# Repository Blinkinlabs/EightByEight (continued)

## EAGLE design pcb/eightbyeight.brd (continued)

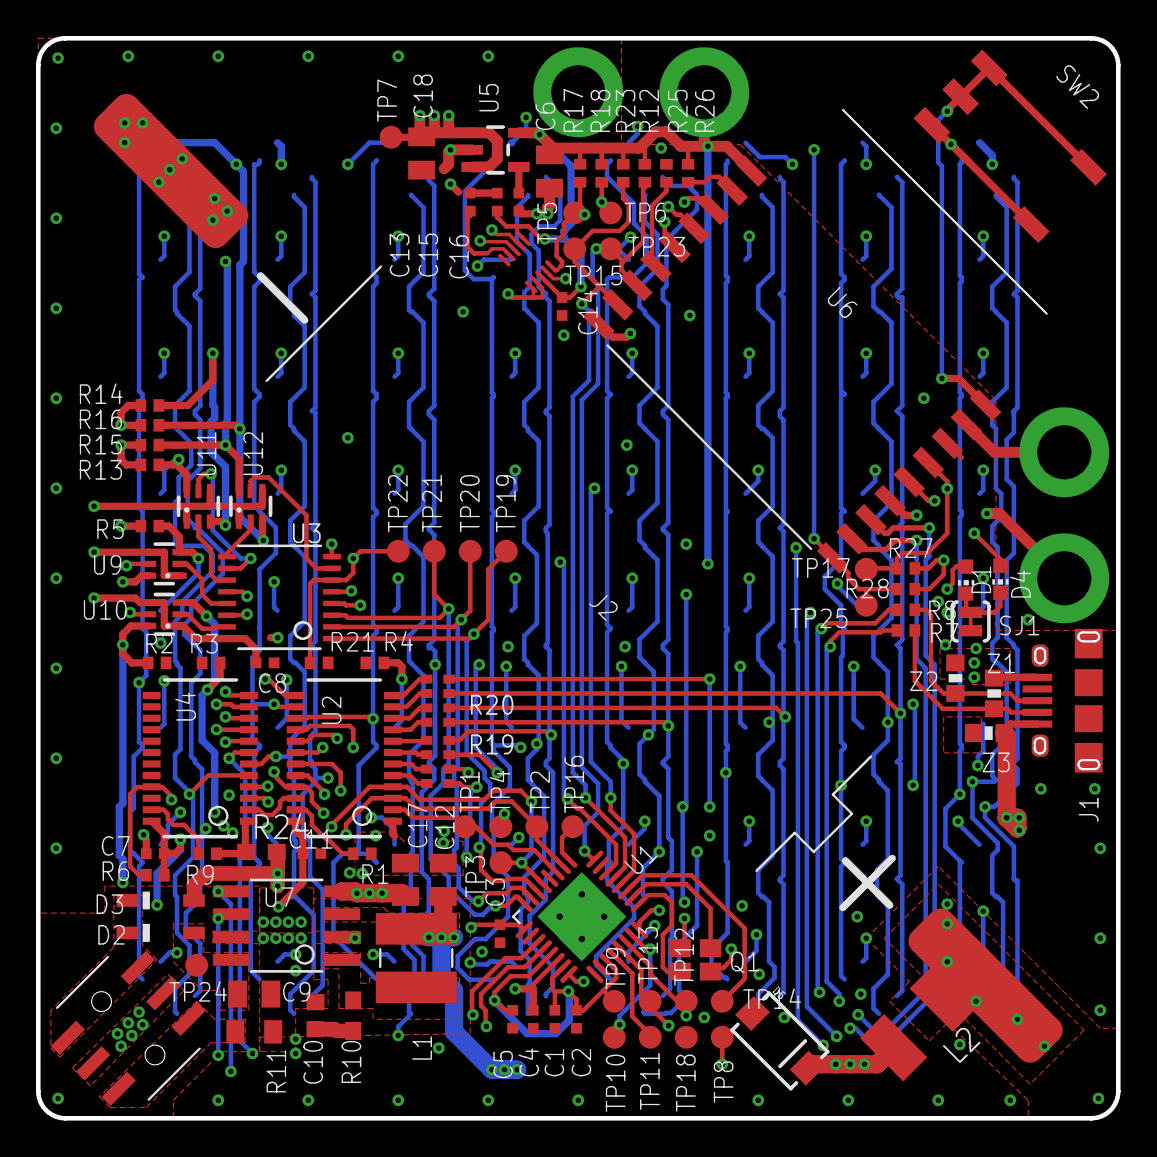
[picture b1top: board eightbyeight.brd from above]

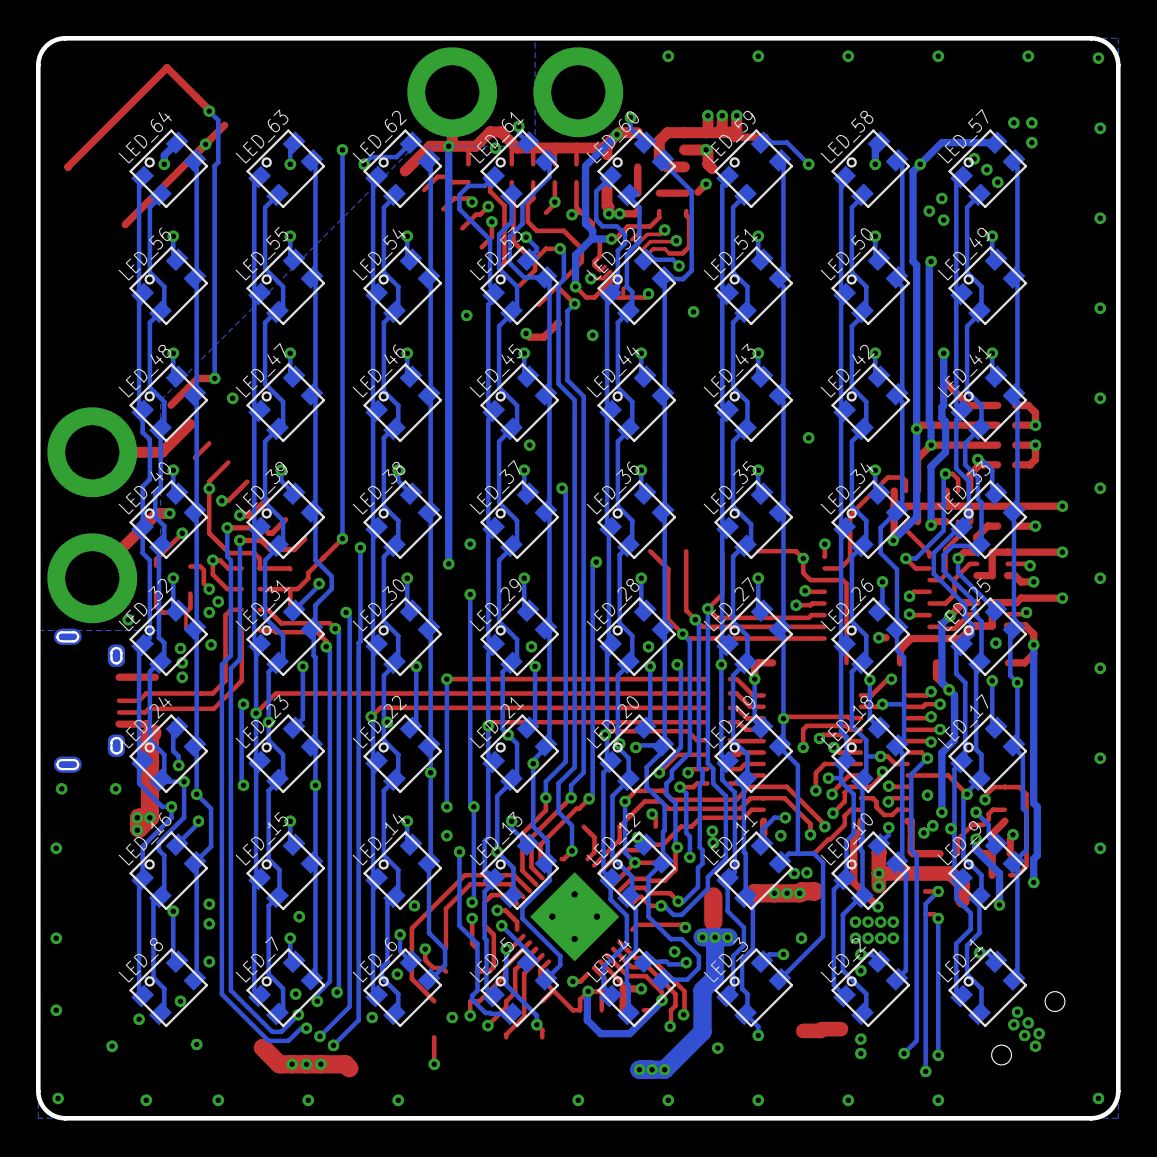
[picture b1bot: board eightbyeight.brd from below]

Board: 4 copper layers, 60.0 x 60.0 mm, 166 parts (64 on the bottom side), 99 nets.

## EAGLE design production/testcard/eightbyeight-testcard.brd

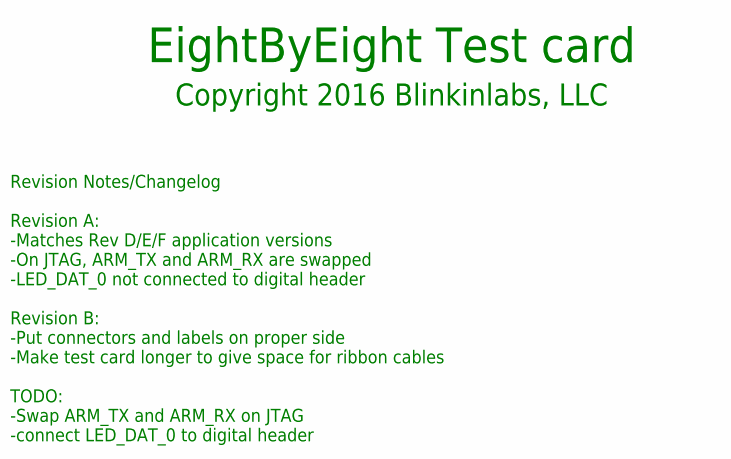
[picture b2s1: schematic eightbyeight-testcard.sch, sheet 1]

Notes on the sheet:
Revision Notes/Changelog Revision A: -Matches Rev D/E/F application versions -On JTAG, ARM_TX and ARM_RX are swapped -LED_DAT_0 not connected to digital header Revision B: -Put connectors and labels on proper side -Make test card longer to give space for ribbon cables TODO: -Swap ARM_TX and ARM_RX 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
EightByEight Test card
Copyright 2016 Blinkinlabs, LLC

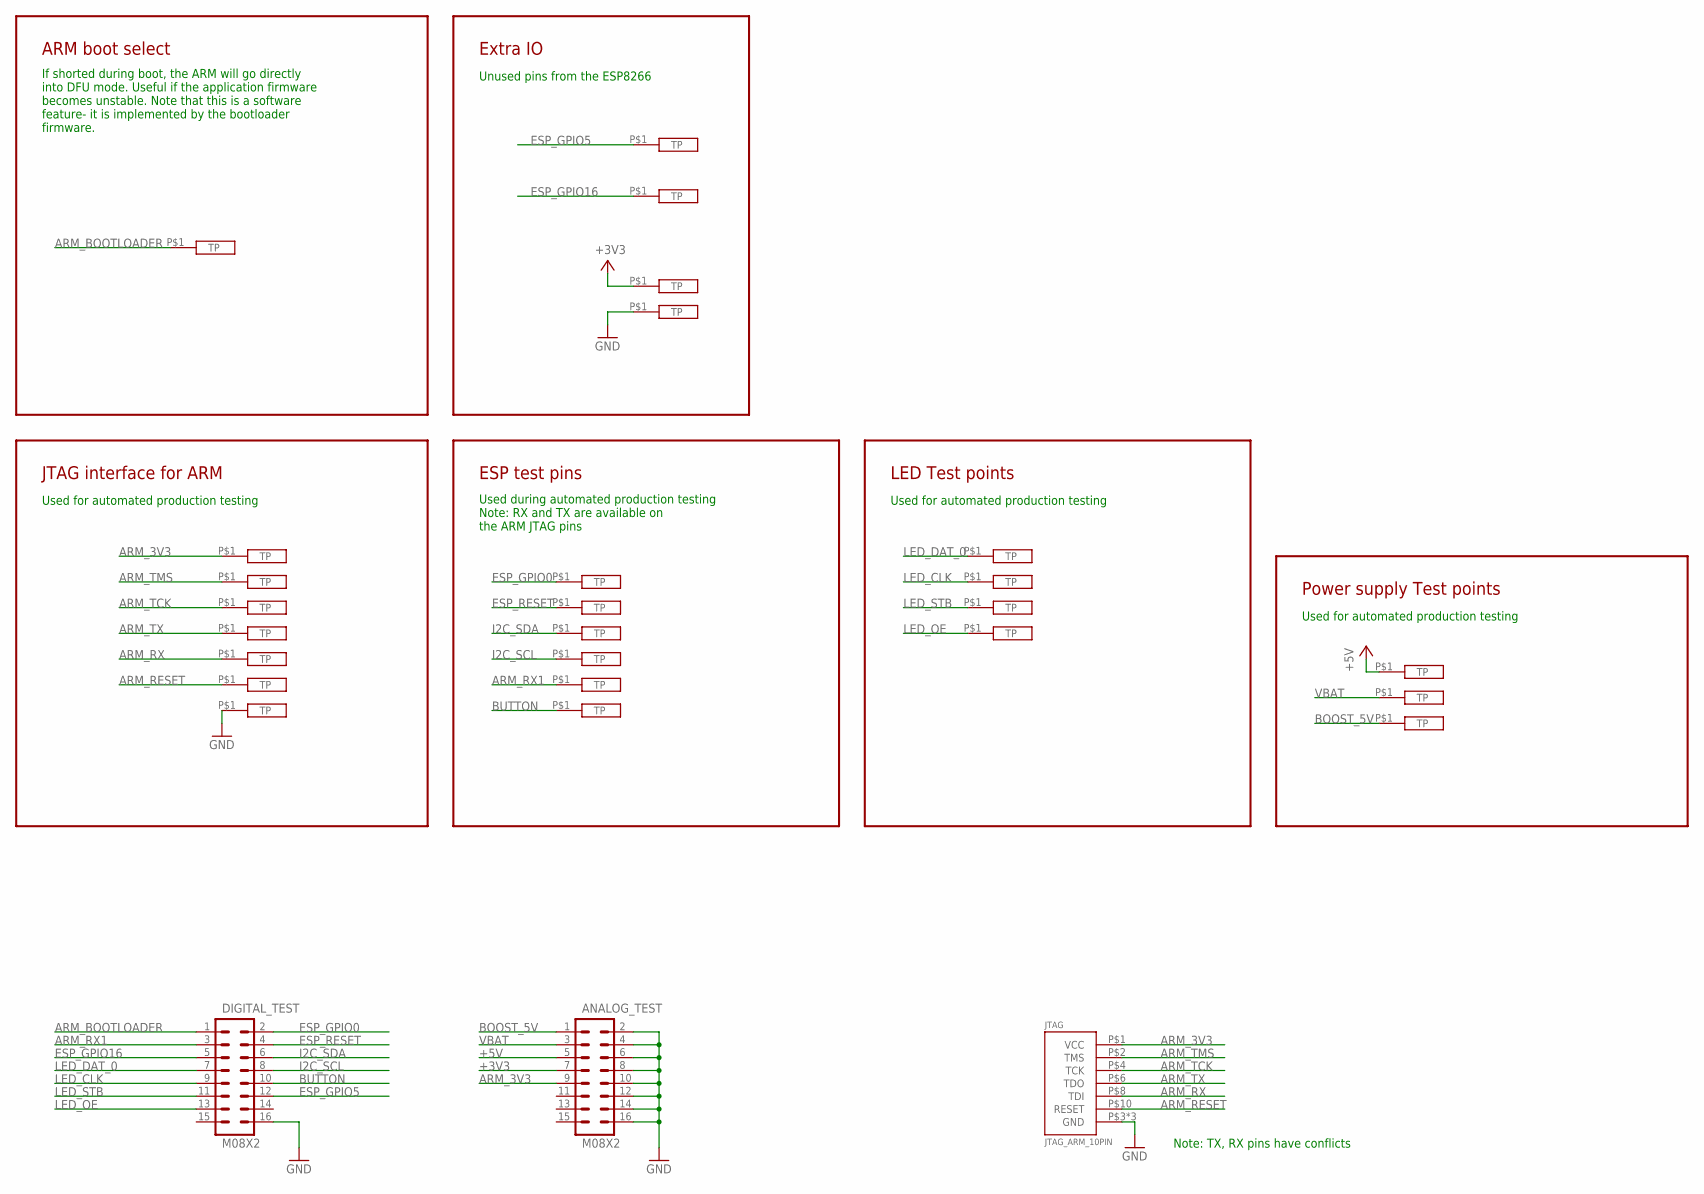
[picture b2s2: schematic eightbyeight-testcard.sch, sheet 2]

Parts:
5V: TEST_POINT1.4MM; IO_HOLE_1.4MM
+3V3: TEST_POINT2.55MM; IO_HOLE_2.55MM
ANALOG_TEST: M08X2; 2X8
ARM_3V3: TEST_POINT1.4MM; IO_HOLE_1.4MM
ARM_BOOT: TEST_POINT1.4MM; IO_HOLE_1.4MM
ARM_RESET: TEST_POINT1.4MM; IO_HOLE_1.4MM
ARM_RX, ARM_RX1: TEST_POINT1.4MM; IO_HOLE_1.4MM
ARM_TCK: TEST_POINT1.4MM; IO_HOLE_1.4MM
ARM_TMS: TEST_POINT1.4MM; IO_HOLE_1.4MM
ARM_TX: TEST_POINT1.4MM; IO_HOLE_1.4MM
BOOST_5V: TEST_POINT1.4MM; IO_HOLE_1.4MM
BUTTON: TEST_POINT1.4MM; IO_HOLE_1.4MM
DIGITAL_TEST: M08X2; 2X8
ESP_GPIO0: TEST_POINT1.4MM; IO_HOLE_1.4MM
ESP_GPIO5, ESP_GPIO16: TEST_POINT2.55MM; IO_HOLE_2.55MM
ESP_RESET: TEST_POINT1.4MM; IO_HOLE_1.4MM
GND: TEST_POINT2.55MM; IO_HOLE_2.55MM
GND_: TEST_POINT1.4MM; IO_HOLE_1.4MM
I2C_SCL, I2C_SDA: TEST_POINT1.4MM; IO_HOLE_1.4MM
JTAG: JTAG_ARM_10PIN; 2X05-1.27MM-SMD
LED_CLK: TEST_POINT1.4MM; IO_HOLE_1.4MM
LED_DATA: TEST_POINT1.4MM; IO_HOLE_1.4MM
LED_OE: TEST_POINT1.4MM; IO_HOLE_1.4MM
LED_STB: TEST_POINT1.4MM; IO_HOLE_1.4MM
VBAT: TEST_POINT1.4MM; IO_HOLE_1.4MM

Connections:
+3V3: +3V3.P$1, ANALOG_TEST.7
+5V: 5V.P$1, ANALOG_TEST.5
ARM_3V3: ANALOG_TEST.9, ARM_3V3.P$1, JTAG.P$1 (VCC)
ARM_BOOTLOADER: ARM_BOOT.P$1, DIGITAL_TEST.1
ARM_RESET: ARM_RESET.P$1, JTAG.P$10 (RESET)
ARM_RX: ARM_RX.P$1, JTAG.P$8 (TDI)
ARM_RX1: ARM_RX1.P$1, DIGITAL_TEST.3
ARM_TCK: ARM_TCK.P$1, JTAG.P$4 (TCK)
ARM_TMS: ARM_TMS.P$1, JTAG.P$2 (TMS)
ARM_TX: ARM_TX.P$1, JTAG.P$6 (TDO)
BOOST_5V: ANALOG_TEST.1, BOOST_5V.P$1
BUTTON: BUTTON.P$1, DIGITAL_TEST.10
ESP_GPIO0: DIGITAL_TEST.2, ESP_GPIO0.P$1
ESP_GPIO5: DIGITAL_TEST.12, ESP_GPIO5.P$1
ESP_GPIO16: DIGITAL_TEST.5, ESP_GPIO16.P$1
ESP_RESET: DIGITAL_TEST.4, ESP_RESET.P$1
GND: ANALOG_TEST.2, ANALOG_TEST.4, ANALOG_TEST.6, ANALOG_TEST.8, ANALOG_TEST.10, ANALOG_TEST.12, ANALOG_TEST.14, ANALOG_TEST.16, DIGITAL_TEST.16, GND.P$1, GND_.P$1, JTAG.P$3 (GND), JTAG.P$5 (GND), JTAG.P$9 (GND)
I2C_SCL: DIGITAL_TEST.8, I2C_SCL.P$1
I2C_SDA: DIGITAL_TEST.6, I2C_SDA.P$1
LED_CLK: DIGITAL_TEST.9, LED_CLK.P$1
LED_DAT_0: DIGITAL_TEST.7, LED_DATA.P$1
LED_OE: DIGITAL_TEST.13, LED_OE.P$1
LED_STB: DIGITAL_TEST.11, LED_STB.P$1
VBAT: ANALOG_TEST.3, VBAT.P$1

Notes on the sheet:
If shorted during boot, the ARM will go directly into DFU mode. Useful if the application firmware becomes unstable. Note that this is a software feature- it is implemented by the bootloader firmware.
ARM boot select
Used for automated production testing
JTAG interface for ARM
Unused pins from the ESP8266
Extra IO
Used during automated production testing Note: RX and TX are available on the ARM JTAG pins
ESP test pins
Power supply Test points
LED Test points
Note: TX, RX pins have conflicts

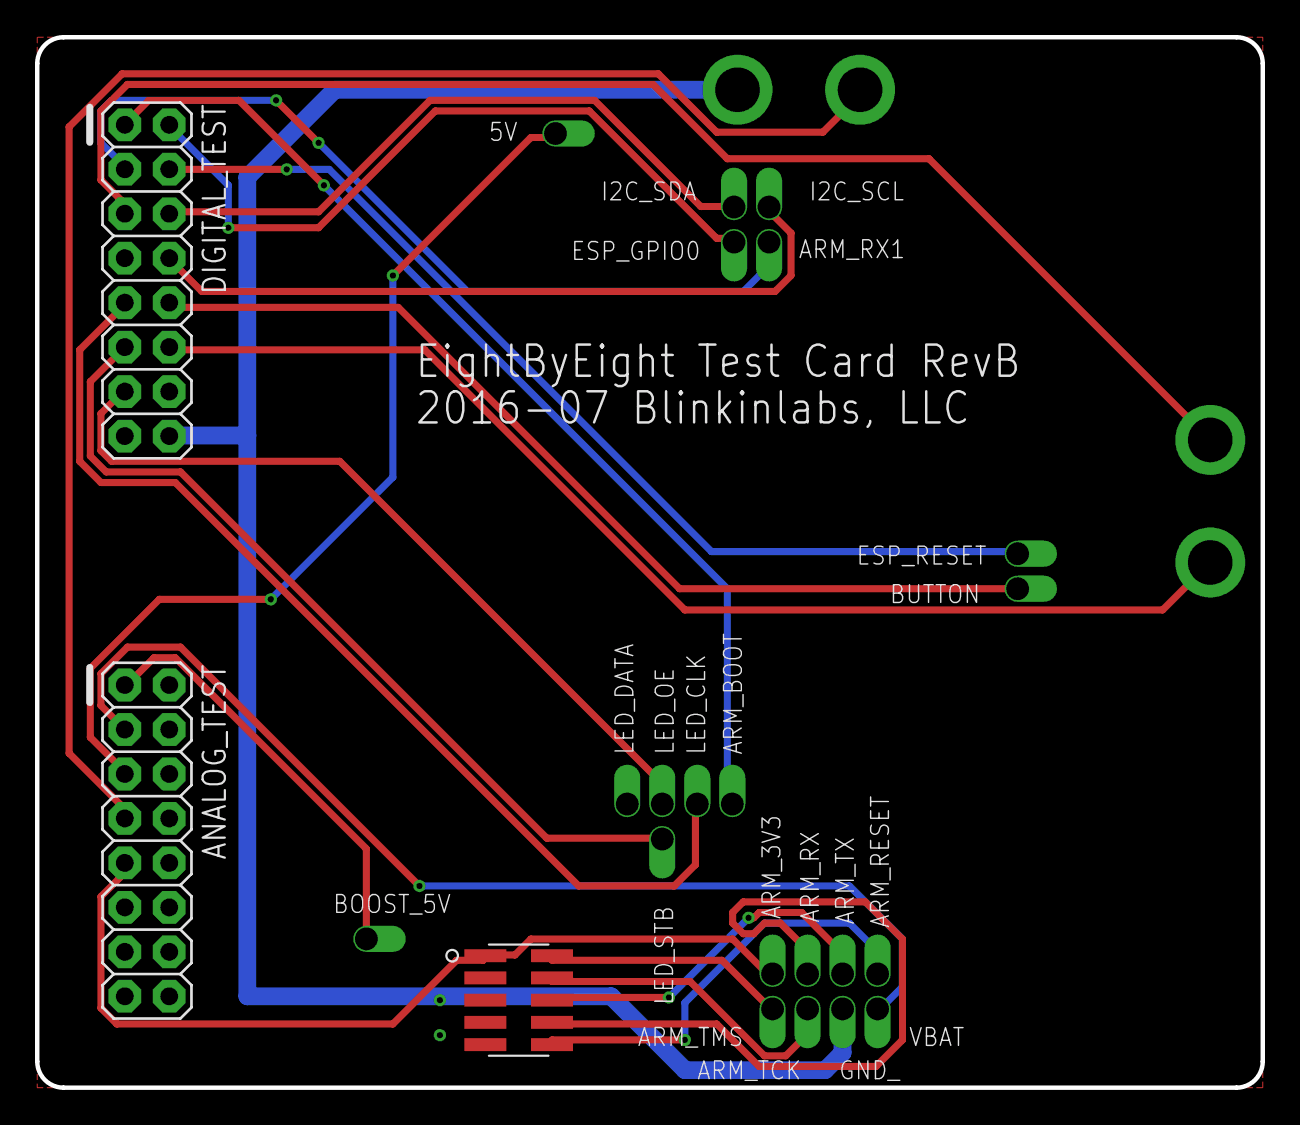
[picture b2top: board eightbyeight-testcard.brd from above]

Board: 2 copper layers, 70.0 x 60.0 mm, 28 parts (1 on the bottom side), 24 nets.

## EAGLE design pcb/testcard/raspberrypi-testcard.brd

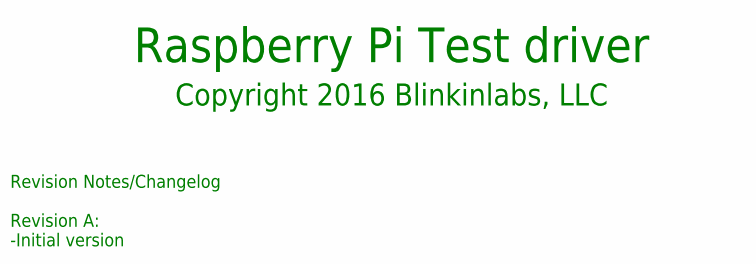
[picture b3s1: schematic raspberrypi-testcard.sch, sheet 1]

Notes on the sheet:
Revision Notes/Changelog Revision A: -Initial version
Raspberry Pi Test driver
Copyright 2016 Blinkinlabs, LLC

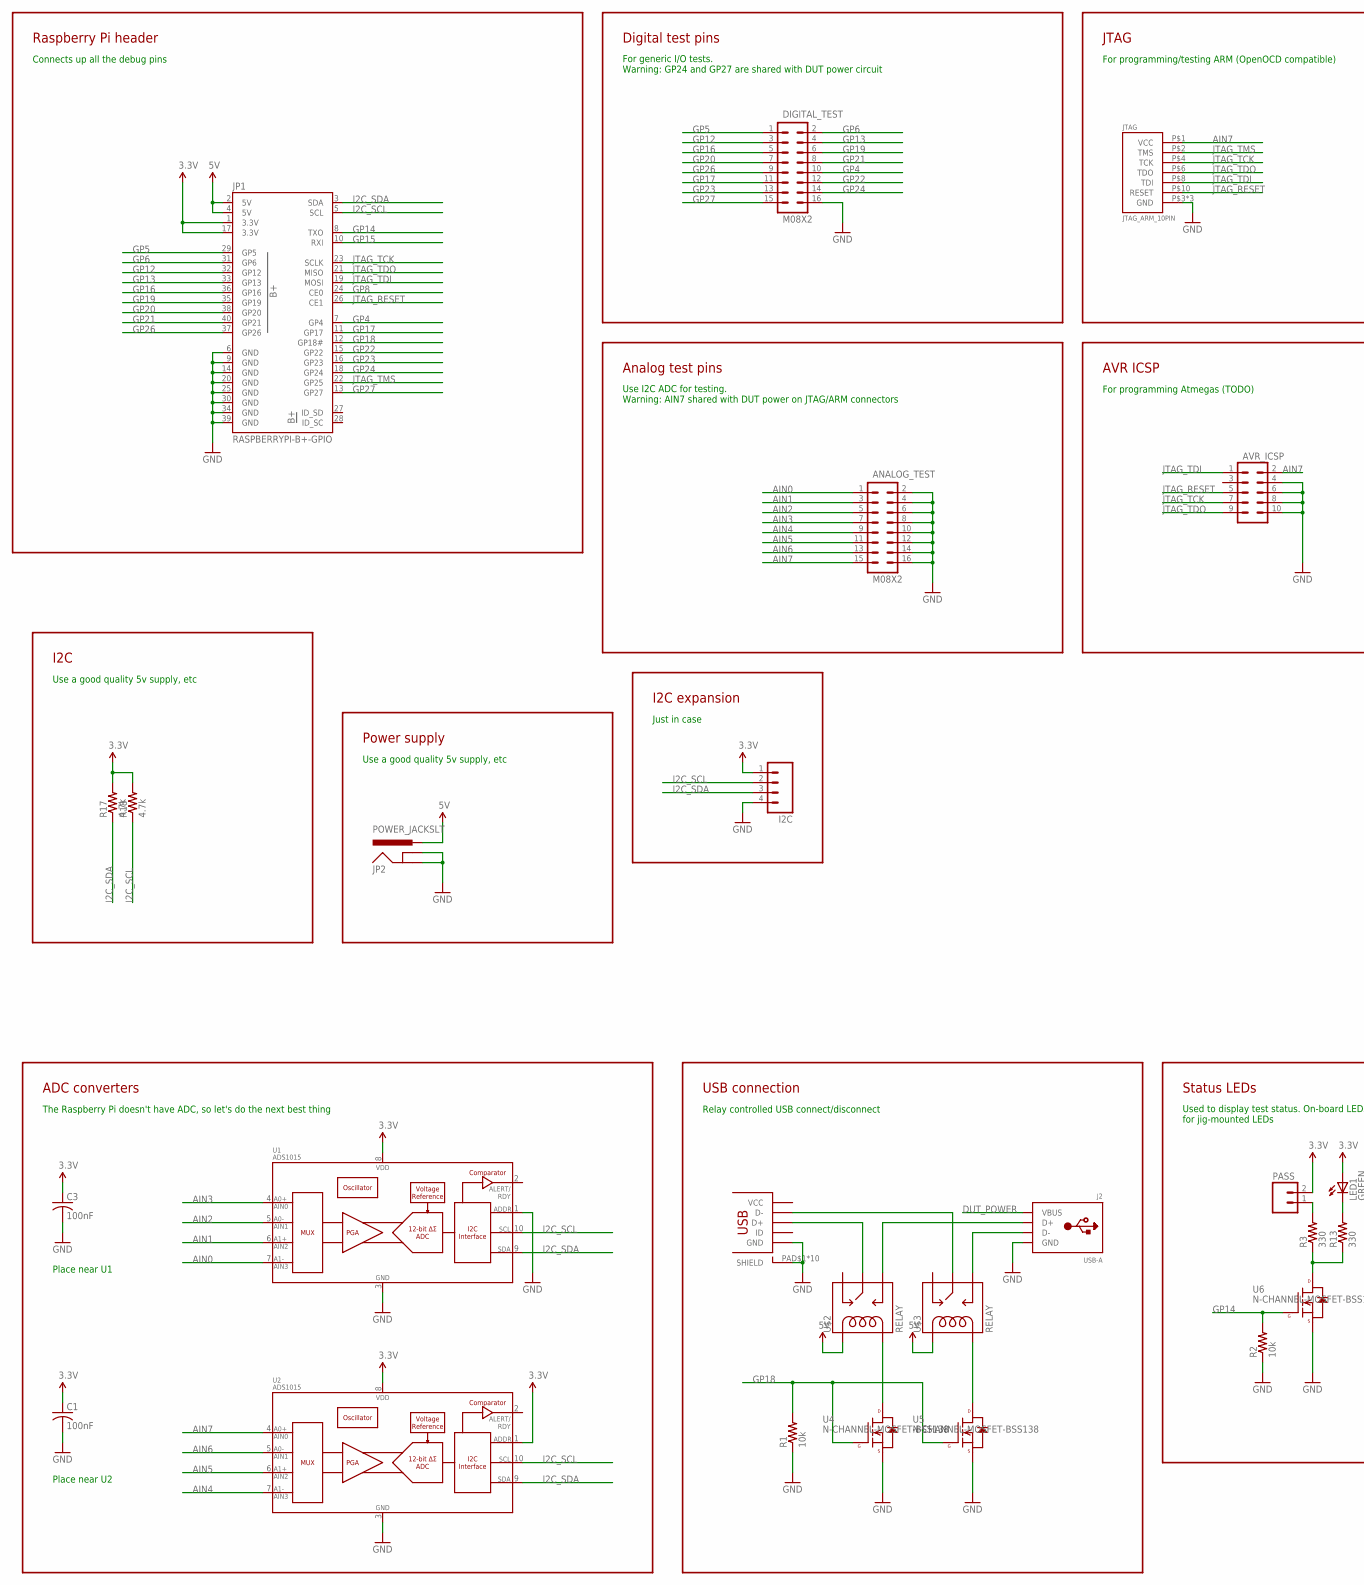
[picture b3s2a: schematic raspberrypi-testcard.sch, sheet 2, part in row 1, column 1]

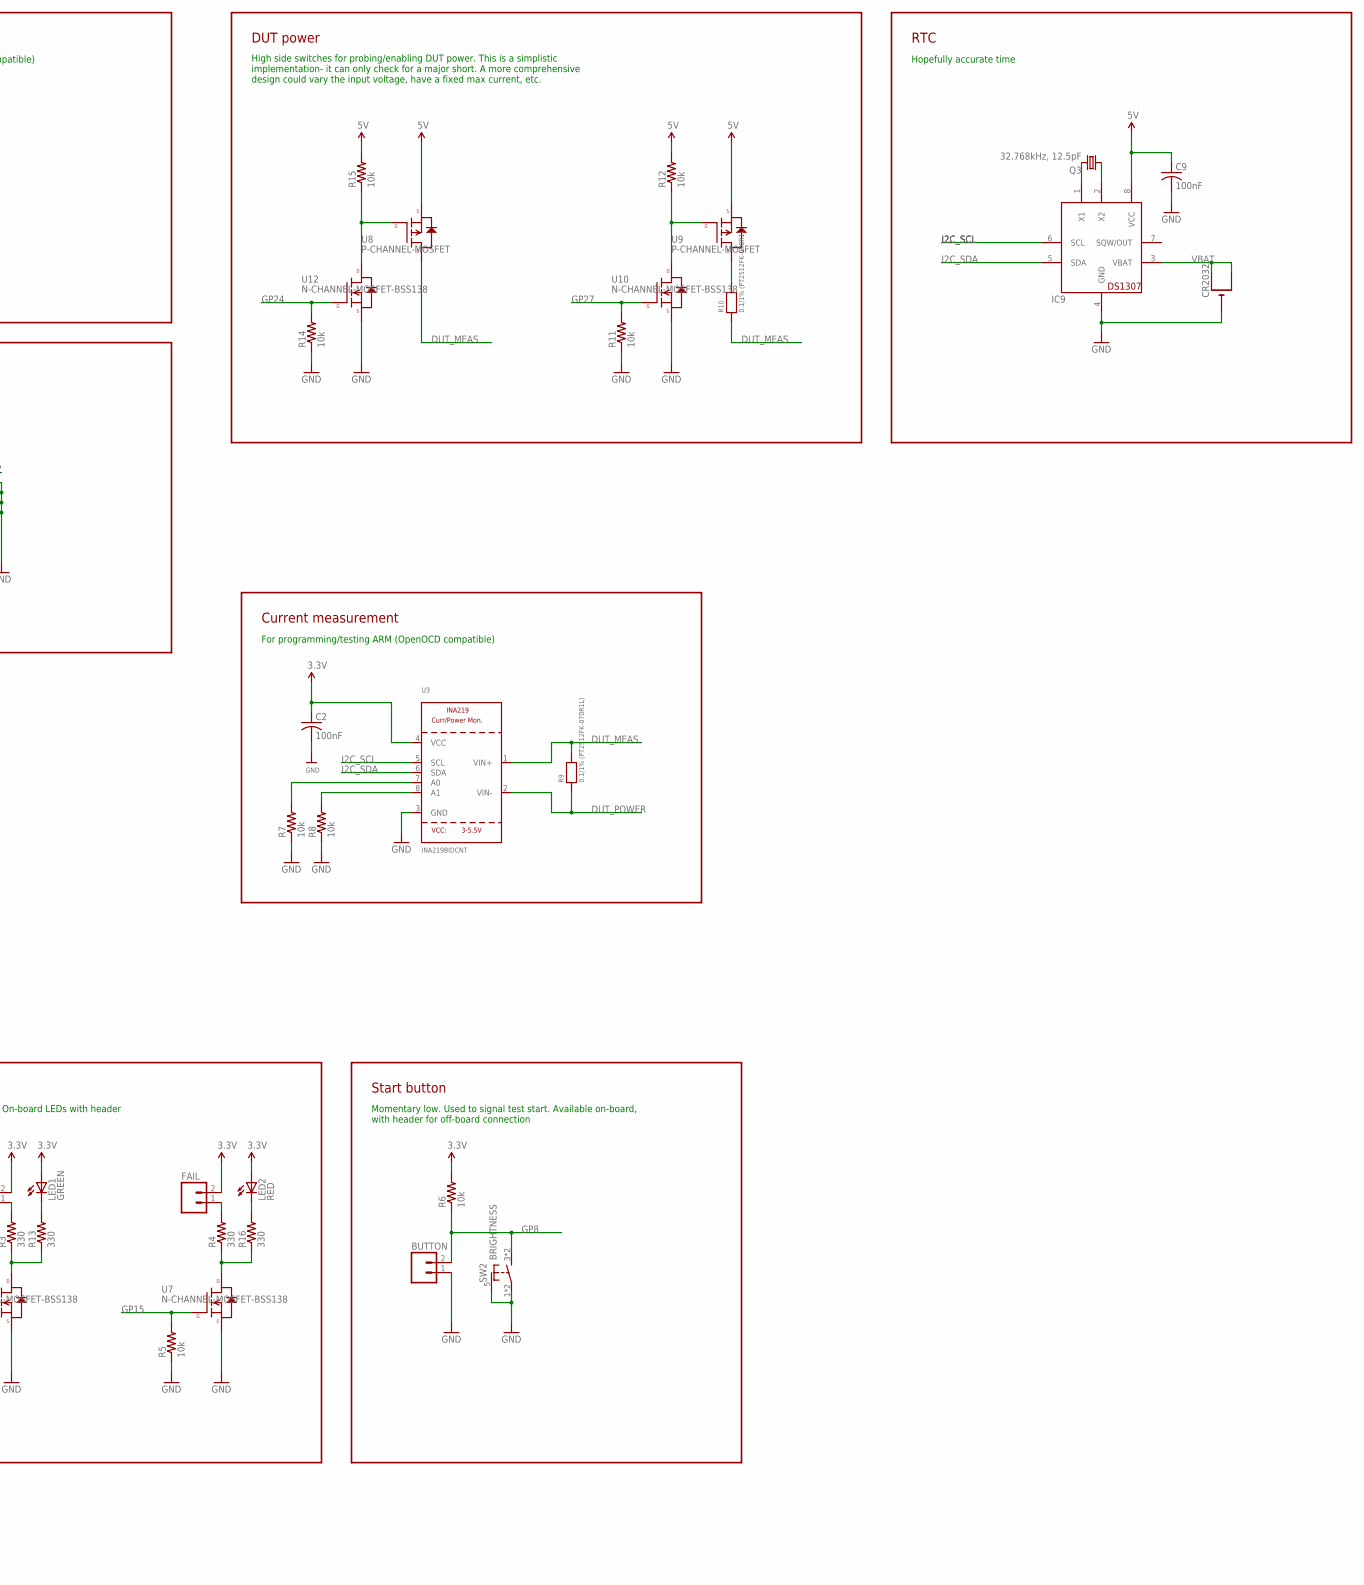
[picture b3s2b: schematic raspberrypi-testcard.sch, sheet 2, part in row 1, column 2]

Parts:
ANALOG_TEST: M08X2; 2X8
AVR_ICSP: M05X2PTH; AVR_ICSP
BUTTON: M02JST-PTH-2; JST-2-PTH
C1, C2, C3: 100nF; C0402
C9: 100nF; C0402K
CR2032: CR2032SMT; CR2032-SMD
DIGITAL_TEST: M08X2; 2X8
FAIL: M02JST-PTH-2; JST-2-PTH
I2C: M04PTH; 1X04
IC9: DS1307SO08; SO08-150
J1: USB_MICROSMT+THRUHULE; USB_MICRO_THRUHOLE
J2: USB-A; MOLEX_480371000
JP1: RASPBERRYPI-B+-GPIO; 2X20-SHROUDED
JP2: POWER_JACKSLT; POWER_JACK_SLOT
JTAG: JTAG_ARM_10PIN; 2X05-1.27MM-SMD
LED1: GREEN; CHIP-LED0805
LED2: RED; CHIP-LED0805
PASS: M02JST-PTH-2; JST-2-PTH
Q3: 32.768kHz, 12.5pF; TC26H
R1, R2, R5, R6, R7, R8, R11, R12, R14, R15: 10k; R0402
R3, R4, R13, R16: 330; R0402
R9, R10: 0.1/1% (PT2512FK-070R1L); 2512
R17, R18: 4.7k; R0402
SW2: BRIGHTNESS; TD-07XB
U1, U2: ADS1015; MSOP10
U3: INA219BIDCNT; SOT23-8
U4, U5, U6, U7, U10, U12: N-CHANNEL-MOSFET-BSS138; SOT23-3
U8, U9: P-CHANNEL-MOSFET; SOT23-3
U$2, U$3: RELAY; RELAY_HK23F-5V

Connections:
AIN0: ANALOG_TEST.1, U1.7 (AIN3)
AIN1: ANALOG_TEST.3, U1.6 (AIN2)
AIN2: ANALOG_TEST.5, U1.5 (AIN1)
AIN3: ANALOG_TEST.7, U1.4 (AIN0)
AIN4: ANALOG_TEST.9, U2.7 (AIN3)
AIN5: ANALOG_TEST.11, U2.6 (AIN2)
AIN6: ANALOG_TEST.13, U2.5 (AIN1)
AIN7: ANALOG_TEST.15, AVR_ICSP.2, JTAG.P$1 (VCC), U2.4 (AIN0)
DUT_MEAS: R9.2, R10.1, U3.1 (VIN+), U8.3 (D)
DUT_POWER: J2.1 (VBUS), R9.1, U3.2 (VIN-)
GND: ANALOG_TEST.2, ANALOG_TEST.4, ANALOG_TEST.6, ANALOG_TEST.8, ANALOG_TEST.10, ANALOG_TEST.12, ANALOG_TEST.14, ANALOG_TEST.16, AVR_ICSP.4, AVR_ICSP.6, AVR_ICSP.8, AVR_ICSP.10, BUTTON.1, C1.2, C2.2, C3.2, C9.2, CR2032.-, DIGITAL_TEST.16, I2C.4, IC9.4 (GND), J1.PAD$1 (SHIELD), J1.PAD$2 (SHIELD), J1.PAD$3 (SHIELD), J1.PAD$4 (SHIELD), J1.PAD$5 (SHIELD), J1.PAD$6 (SHIELD), J1.PAD$7 (SHIELD), J1.PAD$8 (SHIELD), J1.PAD$9 (SHIELD), J1.PAD$10 (SHIELD), J1.PIN$5 (GND), J2.4 (GND), JP1.6 (GND), JP1.9 (GND), JP1.14 (GND), JP1.20 (GND), JP1.25 (GND), JP1.30 (GND), JP1.34 (GND), JP1.39 (GND), JP2.GND@1 (GNDBREAK), JP2.GND@2 (GND), JTAG.P$3 (GND), JTAG.P$5 (GND), JTAG.P$9 (GND), R1.1, R2.1, R5.1, R7.1, R8.1, R11.1, R14.1, SW2.1, SW2.2, SW2.5 (SHIELD), U1.1 (ADDR), U1.3 (VSS), U2.3 (VSS), U3.3 (GND), U4.2 (S), U5.2 (S), U6.2 (S), U7.2 (S), U10.2 (S), U12.2 (S)
GP4: DIGITAL_TEST.10, JP1.7 (GP4)
GP5: DIGITAL_TEST.1, JP1.29 (GP5)
GP6: DIGITAL_TEST.2, JP1.31 (GP6)
GP8: BUTTON.2, JP1.24 (CE0), R6.1, SW2.3 (S), SW2.4 (S)
GP12: DIGITAL_TEST.3, JP1.32 (GP12)
GP13: DIGITAL_TEST.4, JP1.33 (GP13)
GP14: JP1.8 (TXO), R2.2, U6.1 (G)
GP15: JP1.10 (RXI), R5.2, U7.1 (G)
GP16: DIGITAL_TEST.5, JP1.36 (GP16)
GP17: DIGITAL_TEST.11, JP1.11 (GP17)
GP18: JP1.12 (GP18#), R1.2, U4.1 (G), U5.1 (G)
GP19: DIGITAL_TEST.6, JP1.35 (GP19)
GP20: DIGITAL_TEST.7, JP1.38 (GP20)
GP21: DIGITAL_TEST.8, JP1.40 (GP21)
GP22: DIGITAL_TEST.12, JP1.15 (GP22)
GP23: DIGITAL_TEST.13, JP1.16 (GP23)
GP24: DIGITAL_TEST.14, JP1.18 (GP24), R14.2, U12.1 (G)
GP26: DIGITAL_TEST.9, JP1.37 (GP26)
GP27: DIGITAL_TEST.15, JP1.13 (GP27), R11.2, U10.1 (G)
I2C_SCL: I2C.2, IC9.6 (SCL), JP1.5 (SCL), R18.1, U1.10 (SCL), U2.10 (SCL), U3.5 (SCL)
I2C_SDA: I2C.3, IC9.5 (SDA), JP1.3 (SDA), R17.1, U1.9 (SDA), U2.9 (SDA), U3.6 (SDA)
JTAG_RESET: AVR_ICSP.5, JP1.26 (CE1), JTAG.P$10 (RESET)
JTAG_TCK: AVR_ICSP.7, JP1.23 (SCLK), JTAG.P$4 (TCK)
JTAG_TDI: AVR_ICSP.1, JP1.19 (MOSI), JTAG.P$8 (TDI)
JTAG_TDO: AVR_ICSP.9, JP1.21 (MISO), JTAG.P$6 (TDO)
JTAG_TMS: JP1.22 (GP25), JTAG.P$2 (TMS)
unnamed: J1.PIN$3 (D+), U$2.P$1 (MAIN), U$2.P$6 (MAIN)
unnamed: J2.3 (D+), U$2.P$3 (NO)
unnamed: J1.PIN$2 (D-), U$3.P$1 (MAIN), U$3.P$6 (MAIN)
unnamed: J2.2 (D-), U$3.P$3 (NO)
unnamed: R4.1, R16.1, U7.3 (D)
unnamed: U5.3 (D), U$3.P$5 (COIL2)
unnamed: U4.3 (D), U$2.P$5 (COIL2)
unnamed: R3.1, R13.1, U6.3 (D)
unnamed: R8.2, U3.8 (A1)
unnamed: FAIL.1, R4.2
unnamed: PASS.1, R3.2
unnamed: R7.2, U3.7 (A0)
unnamed: R10.2, U9.3 (D)
unnamed: R12.1, U9.1 (G), U10.3 (D)
unnamed: LED2.C, R16.2
unnamed: R15.1, U8.1 (G), U12.3 (D)
unnamed: LED1.C, R13.2
unnamed: IC9.1 (X1), Q3.2
unnamed: IC9.2 (X2), Q3.1
VBAT: CR2032.+$1 (+), CR2032.+$2 (+1), IC9.3 (VBAT)

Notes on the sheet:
Connects up all the debug pins
Raspberry Pi header
For generic I/O tests. Warning: GP24 and GP27 are shared with DUT power circuit
Digital test pins
Use I2C ADC for testing. Warning: AIN7 shared with DUT power on JTAG/ARM connectors
Analog test pins
For programming/testing ARM (OpenOCD compatible)
JTAG
For programming Atmegas (TODO)
AVR ICSP
The Raspberry Pi doesn't have ADC, so let's do the next best thing
ADC converters
USB connection
Relay controlled USB connect/disconnect
Power supply
Use a good quality 5v supply, etc
Place near U1
Place near U2
I2C
Status LEDs
Used to display test status. On-board LEDs with header for jig-mounted LEDs
Start button
Momentary low. Used to signal test start. Available on-board, with header for off-board connection
Just in case
I2C expansion
Current measurement
High side switches for probing/enabling DUT power. This is a simplistic implementation- it can only check for a major short. A more comprehensive design could vary the input voltage, have a fixed max current, etc.
DUT power
Hopefully accurate time
RTC

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
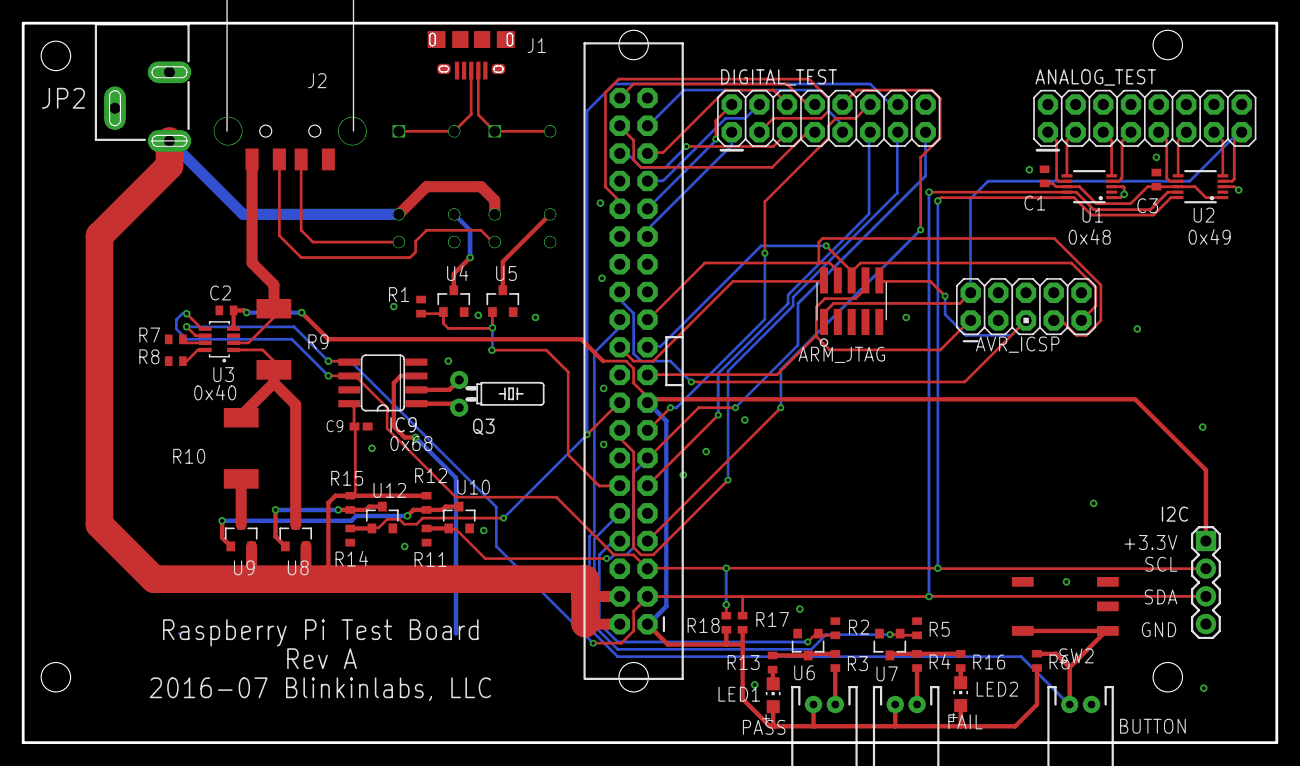
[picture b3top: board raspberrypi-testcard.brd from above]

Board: 2 copper layers, 115.0 x 66.0 mm, 53 parts (1 on the bottom side), 59 nets.

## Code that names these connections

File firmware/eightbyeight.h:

/*
 * Peripherals for the EightByEight Blinky Badge
 *
 * Copyright (c) 2016 Blinkinlabs, LLC
 * 
 * Permission is hereby granted, free of charge, to any person obtaining a copy of
 * this software and associated documentation files (the "Software"), to deal in
 * the Software without restriction, including without limitation the rights to
 * use, copy, modify, merge, publish, distribute, sublicense, and/or sell copies of
 * the Software, and to permit persons to whom the Software is furnished to do so,
 * subject to the following conditions:
 * 
 * The above copyright notice and this permission notice shall be included in all
 * copies or substantial portions of the Software.
 * 
 * THE SOFTWARE IS PROVIDED "AS IS", WITHOUT WARRANTY OF ANY KIND, EXPRESS OR
 * IMPLIED, INCLUDING BUT NOT LIMITED TO THE WARRANTIES OF MERCHANTABILITY, FITNESS
 * FOR A PARTICULAR PURPOSE AND NONINFRINGEMENT. IN NO EVENT SHALL THE AUTHORS OR
 * COPYRIGHT HOLDERS BE LIABLE FOR ANY CLAIM, DAMAGES OR OTHER LIABILITY, WHETHER
 * IN AN ACTION OF CONTRACT, TORT OR OTHERWISE, ARISING FROM, OUT OF OR IN
 * CONNECTION WITH THE SOFTWARE OR THE USE OR OTHER DEALINGS IN THE SOFTWARE.
 */

#ifndef EIGHTBYEIGHT_H
#define EIGHTBYEIGHT_H

#include "mk20dn64.h"

#define LED_COLS 8          // Number of columns that the LED matrix has
#define LED_ROWS 8          // Number of rows that the LED matrix has
#define BYTES_PER_PIXEL     3

#define LED_COUNT           (LED_COLS*LED_ROWS)  // Number of LEDs we are controlling

// Output assignments
// Note: These can't be changed arbitrarily- the GPIOs are actually
// referred to in the library by their port assignments. They are noted
// here for reference.
#define LED_HS_EN_PIN   7   // PC1
//#define LED_CLOCK_PIN   11  // SPI0 CLK / PC6
//#define LED_DATA_PIN    12  // SPI0 MOSI / PC5
//#define LED_STROBE_PIN  14  // FTM0 channel 4 / PD4
//#define LED_OE_PIN      4   // FTM0 channel 1 / PA4
#define S0              15  // PD5
#define S1              16  // PD6
#define S2              17  // PD7

#define ESP_RESET_PIN   5 // PB0
#define ESP_GPIO0_PIN   6 // PB1

// Initialize the board hardware
extern void initBoard();

// Refresh the watchdog, so that the board doesn't reset
static inline void watchdog_refresh(void)
{
    __disable_irq();
    WDOG_REFRESH = 0xA602;
    WDOG_REFRESH = 0xB480;
    __enable_irq();
}

#endif

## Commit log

2016-06-01 Import firmware from LeoBlinky
2016-06-02 Firmware that flashes the lights in some form
2016-06-02 Pull in Revision A of the schematic
2016-06-02 Datasheets!
2016-06-02 Concept design and sizing
2016-06-02 First blink! Matrix running in 8-bit RGB mode, with python example
2016-06-02 Use BlinkyTape protocol from BlinkyPendant
2016-06-02 Write incoming serial data directly to the back buffer
2016-06-02 Add flash memory writing features, plumbing for animation storage
2016-06-02 Clean up label placements on PCB
2016-06-18 Convert matrix interface to a class
2016-06-21 Routing changes on PCB, cleanup
2016-06-22 Proper datasheet for the ARM (32 pin, not 48 pin)
2016-06-23 Add datasheets for inductors, battery
2016-06-23 Simple usb to serial forwarding
2016-06-23 Add gitignore file
2016-06-23 Continue implementing changes from TODO
2016-06-23 Fix serial description length
2016-06-23 Finish routing accelerometer changes
2016-06-23 USB to serial conversion works at high speeds (not low ones though!)
2016-06-24 Implement LED control over UART1
2016-06-24 PCB: Add LED_OE to row driver mux enable
2016-06-24 Add example firmware for ESP8266 (upload with Arduino)
2016-06-25 Add LED_HS_EN. Increase number of vias on power lines
2016-06-25 Finish placing power diodes and clear DRC errors
2016-06-25 Add discharge LED, finish board routing!
2016-06-25 Label the LEDs
2016-06-28 Add ICN2012 design version
2016-06-29 Add new datasheets
2016-06-29 Update ICN2012 version with new accelerometer
2016-06-29 Finish laying out accelerometer, minor updates to part values/reference designators
2016-06-30 Add getting started guide
2016-06-30 Remove outdated icn2026 datasheet
2016-06-30 Update notes for RevC version
2016-06-30 Rename arduino demo sketch
2016-06-30 Decrease the minimum timing for matrix refresh
2016-06-30 Add 3v and 5v todos for schematic
2016-06-30 Clean up revb schematic
2016-06-30 RevB PCB (pcb/eightbyeight.brd)
2016-06-30 Update the concept design part
2016-06-30 Move the reference documentation
2016-07-01 Update arduino examples
2016-07-01 Update arm firmware for revb board
2016-07-01 Update board TODOs
2016-07-01 Update gitignore to skip files with passwords in them
2016-07-04 Show color swirl by default at boot
2016-07-04 Silkscreen tweaks to pcbs
2016-07-04 Ignore more temporary files
2016-07-04 Pull in bootloader from BlinkyTile, modify DFU pin, disable LED function, and change USB identifier
2016-07-04 linker: fix size of application flash
2016-07-04 Switch to SPI-based matrix output, bump to 13 bit
2016-07-04 Half-working attempt at 12 bit spi writes (10% faster than 8 bit)
2016-07-08 Remove setup delay in arm firmware, optimize matrix code
2016-07-08 Update example wifi firmware
2016-07-08 Add (nonworking) RevC design
2016-07-08 Test pads in progress
2016-07-08 Bugfix: bootloader now honors recovery pin state
2016-07-08 Slim down memory usage to fit in a 8k part
2016-07-08 Switch to a 10-bit table for the moment for higher refresh rate
2016-07-08 Drop the DFU functions
2016-07-08 Closer to RevD
2016-07-08 Final RevD
2016-07-09 Work in progress: LED output broken, pixels >127 wrap to next pixel
2016-07-09 Clean up board silkscreen
2016-07-09 Add matrix controller flow diagram
2016-07-11 Update the examples to accept artnet frames
2016-07-11 Formatting
2016-07-11 Small updates from further testing
2016-07-11 Add teardrop design for RevD
2016-07-11 Add some solidworks case designs
2016-07-11 Add matrix artwork
2016-07-12 Remove old datasheets
2016-07-12 RevE.A
2016-07-13 Rev E, as submitted
2016-07-13 accelerometer test
2016-07-15 import of megademo with all the features
2016-07-16 Switch to 12 bit SPI transactions to save .1uS/bit row write
2016-07-16 Almost back up to speed
2016-07-16 Update test patterns
2016-07-16 Use FTM hardware to generate the strobe signal and save 1 write per PWM cycle
2016-07-16 Matrix almost good to go
2016-07-16 Remove redundant comment
2016-07-16 Update pin descriptions
2016-07-16 Matrix working!
2016-07-16 reduce memory usage: use 16bit values for FTM state changes
2016-07-16 Bugfix
2016-07-16 Matrix: fix first byte alignment
2016-07-16 Broken matrix code, checkpoint
2016-07-18 Remove nonworking INC2012 design
2016-07-18 Add HRC art
2016-07-21 Use correct datasheet for LEDs
2016-07-21 Add test card for PCB
2016-07-21 Production silk and component values
2016-07-22 Remove references to Majenko Technology from boilerplate license file
2016-07-22 Revert X/Y swap in accelerometer: Let's fix that in the code
2016-07-22 Update getting started guide
2016-07-22 Add files for QT creator development
2016-07-22 Push matrix back to 11 bit mode, since the 12th isnt usable
2016-07-22 Use FC-less USB descriptor
2016-07-22 Bugfix: Set timer values properly to avoid noise at startup
2016-07-23 Matrix cleanup
2016-07-24 Update test card to fit new test jig
2016-07-24 Update PWM code to work at 14 bit
2016-07-24 Update test card with proper sized holes
2016-07-25 Add raspberry pi side of test card
2016-07-25 Add CERH OHL license to PCB
2016-07-25 Update testcard to fit current test jig
2016-07-25 Update licenses, clean up includes
2016-07-25 Add placeholder image
2016-07-25 Update readme to use image
2016-07-25 Pull in driver from BlinkyTile (needs updating for new VID/PID)
2016-07-26 Firmware: don't glitch ESP reset line when resetting
2016-07-27 Bring in python-based test program from FlyByNight
2016-07-29 Merge
2016-07-29 Add PIDs from OpenMoko
2016-07-31 Update board errata
2016-07-31 Update test card pcb notes
2016-07-31 Add ESP test firmware
2016-07-31 Bringing up test rig
2016-07-31 Test software work in progress
2016-08-01 Test rig test run
2016-08-01 Color tests
2016-08-02 Test program improvements
2016-08-02 Drop esp test firmware step, add rgbw udp generator
2016-08-03 Show error/failure details
2016-08-03 Some partial instructions for setting up the test rig
2016-08-03 Add serial brightness command
2016-08-03 Add brightness command to matrix library
2016-08-03 Add note about new diode to schematic
2016-08-03 Add test image for v1 firmware
2016-08-03 Move MegaDemo to the arduino directory
2016-08-03 Pull in original MegaDemo code
2016-08-03 Fix rotations in MegaDemo, add setBrightness() command
2016-09-21 better palette
2016-09-21 snake game demo
2016-09-22 Add better flash animation when game is over
2016-09-22 track the entire path, draw it in contrasting colors
2016-09-22 wait before moving after finding the food
2016-09-25 Getting started guide: Use 2MB setting for Arduino upload
2016-09-26 More minor fixes to getting started guide
2016-10-13 Switch to production firmwares
2016-10-13 Rename megademo
2016-10-13 Remove old teset firmware
2016-10-13 Update production instructions
2016-10-18 Update photo to production unit
2016-10-21 Update drivers and attempt to sign them correctly.
2016-10-24 Finish updates
2016-10-24 Fix interface ID in serial driver
2016-10-24 Include cross certificate when signing the driver
2016-10-24 Fix the 'default install' section of the serial driver
2016-10-24 Add brief testing instructions to the readme
2016-10-25 Add battery protection circuit
2016-10-25 Add seperate bleed resistor to 5V input
2016-10-25 Add TODO for resistor/cap sizes
2016-10-25 Add Travis CI script to compile bootlaoder, firmware
2016-10-25 Point to PPA with improved version of toolchain
2016-10-25 Try to force an unauthenticated package
2016-10-25 Add dfu-util to the list of required packages
2016-10-25 Pull in PPA for dfu-util
2016-10-25 Remove hex requirement from make all
2016-10-25 Attempt to add travisci integration for the Arduino examples
2016-10-25 Point to our forked Arduino CI script
2016-10-25 Fix some filename case issues
2016-10-25 Fix artnet receiver so that it at least compiles
2016-10-25 Switch to our flavor of the arduino-travis script
2016-10-25 Remove some unused references from BadgeDemo
2016-10-25 Add .cpp language to travis file
2016-10-25 Add the hex file back to the Makefile
2016-10-26 Move production tests to 'production' folder
2016-10-26 Remove outdated schematics
2016-10-26 Fix reference to arduino examples
2016-10-26 Remove old concept designs
2016-10-26 Remove unengaging accelerometer test
2016-11-22 Add support for the Flaschen Taschen protocol.
    See https://github.com/noisebridge/flaschen-taschen for more info
    about the protocol.
2016-11-29 InternetThing demo, using the MQTT PubSubClient library
2016-11-29 images of setup phase
2016-11-30 Move snake example into proper location
2016-11-30 Add pubsublcient to travis build
2017-02-05 Update production setup instructions with screen rotation
2017-02-12 Replace 0402 components, add RevH notes
2017-02-12 Use copper fills for 5v, battery traces
2017-02-13 Replace caps and resistors
2017-02-13 Teardrop trial before release
2017-02-13 Switch to larger PTC, release RevH
2017-03-16 Add post-production feedback on PCB
2017-03-16 Update art-net receiver
2017-03-16 Add BlinkyDemo (modified version of MegaDemo)
2017-03-17 Fix filename mismatch in ArtNetReceiver
2017-03-17 Fix filename issue in ArtNetReceiver
2017-03-19 ArtNetReceiver: Fix typo
2017-05-13 Remove some outdated examples
2017-05-13 Add colorswirl demo
2017-05-13 Remove old badgedemo example
2017-05-13 60FPS, taps, serial receiver
2017-05-14 Add serial receiver for live serial streaming
2017-05-23 Semi-working serial routines
2017-05-24 Can play back first pattern
2017-05-29 Working pattern uploader!
2017-05-29 Fix file case error
2017-05-29 Revert some changes to Rain, Life
2017-05-29 Add firmware version command
2017-08-09 Update setup instruction
2017-10-26 Improve firmware upload reliability
    -Lower baud rate to 350000 (somewhat arbitrary)
    -Set GPIO0 to input when not in reset procedure
    -Set both RESSET and GPIO0 to pulldown only mode
2019-09-18 Add lasercut frontplate template
2024-02-05 Add dangling examples
